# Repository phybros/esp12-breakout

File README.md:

# Breakout Board for ESP-12E and ESP-12F

This repo contains all the design files to make a breakout board for the ESP-12E and the ESP-12F which will allow you to use the ESP module on a breadboard.

The project was created using KiCAD v6.

## Design Goals

1. Breadboard compatible (i.e. 2.54mm pitch)
1. Breadboard connection doesn't cover all the breadboard holes
1. Max 2-sided PCB
1. As small (read: cheap to fabricate) as possible

## Screenshots/Photos

## License

This repo is licensed under the [Attribution-ShareAlike 4.0 license (CC BY-SA 4.0)](https://creativecommons.org/licenses/by-sa/4.0/)

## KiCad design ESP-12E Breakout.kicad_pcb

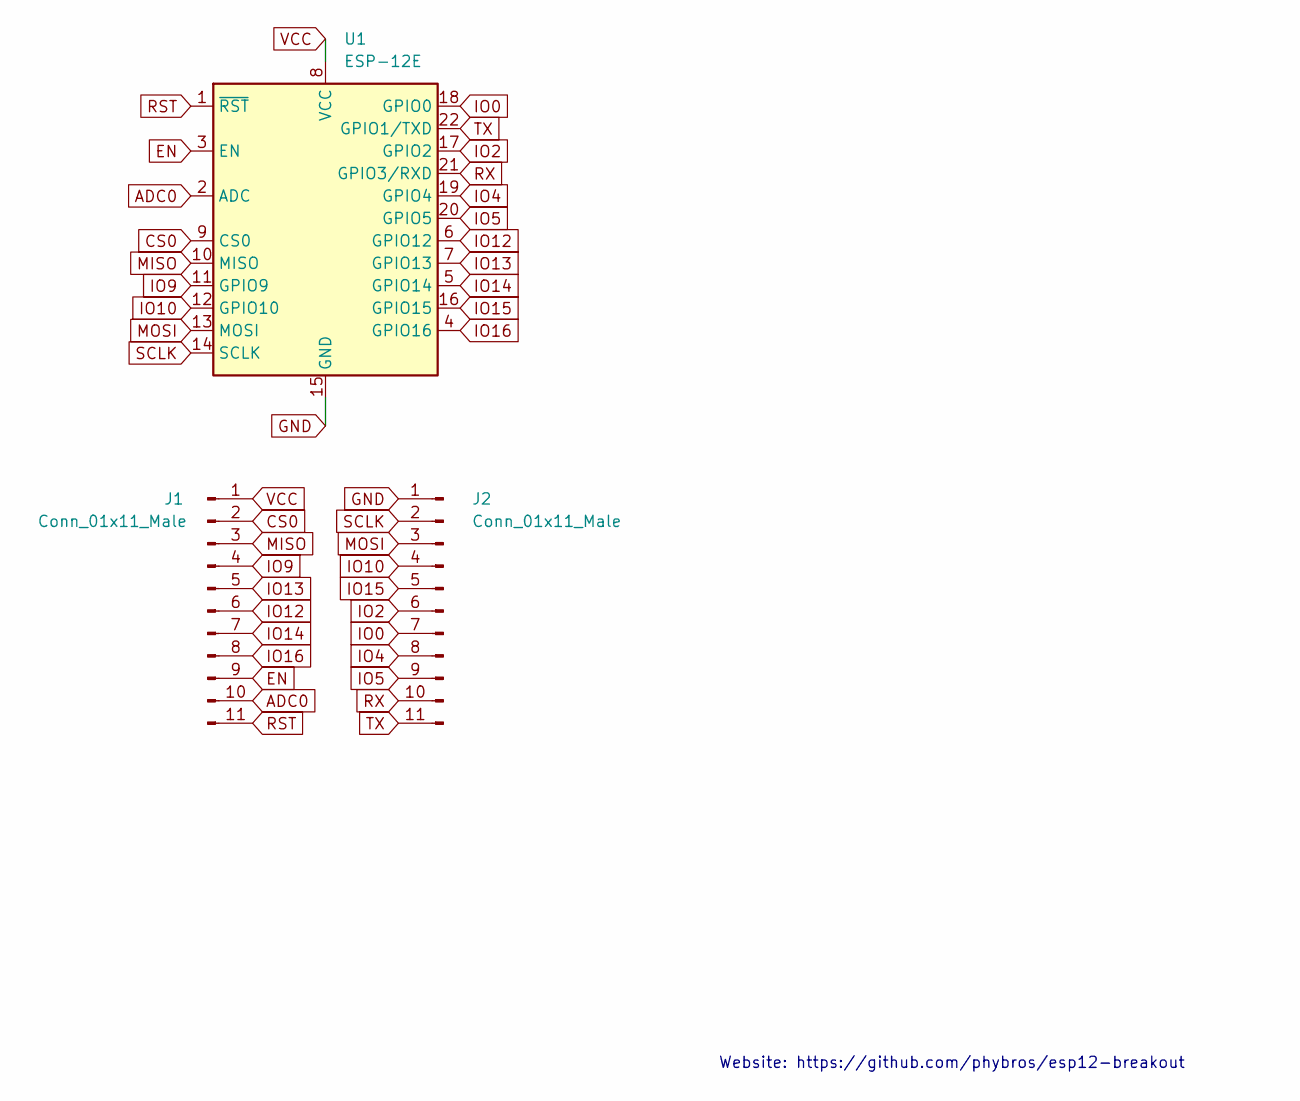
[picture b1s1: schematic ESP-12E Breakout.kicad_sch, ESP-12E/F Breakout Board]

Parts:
J1, J2: Conn_01x11_Male; PinHeader_1x11_P2.54mm_Vertical
U1: ESP-12E

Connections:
ADC0: J1.10, U1.2 (ADC)
CS0: J1.2, U1.9 (CS0)
EN: J1.9, U1.3 (EN)
GND: J2.1, U1.15 (GND)
IO0: J2.7, U1.18 (GPIO0)
IO2: J2.6, U1.17 (GPIO2)
IO4: J2.8, U1.19 (GPIO4)
IO5: J2.9, U1.20 (GPIO5)
IO9: J1.4, U1.11 (GPIO9)
IO10: J2.4, U1.12 (GPIO10)
IO12: J1.6, U1.6 (GPIO12)
IO13: J1.5, U1.7 (GPIO13)
IO14: J1.7, U1.5 (GPIO14)
IO15: J2.5, U1.16 (GPIO15)
IO16: J1.8, U1.4 (GPIO16)
MISO: J1.3, U1.10 (MISO)
MOSI: J2.3, U1.13 (MOSI)
RST: J1.11, U1.1 (~RST)
RX: J2.10, U1.21 (GPIO3/RXD)
SCLK: J2.2, U1.14 (SCLK)
TX: J2.11, U1.22 (GPIO1/TXD)
VCC: J1.1, U1.8 (VCC)

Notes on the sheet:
Website: https://github.com/phybros/esp12-breakout

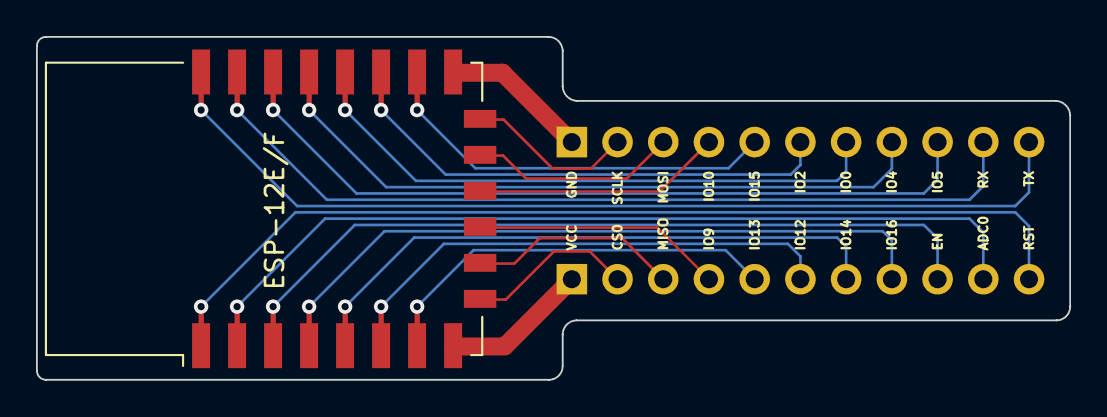
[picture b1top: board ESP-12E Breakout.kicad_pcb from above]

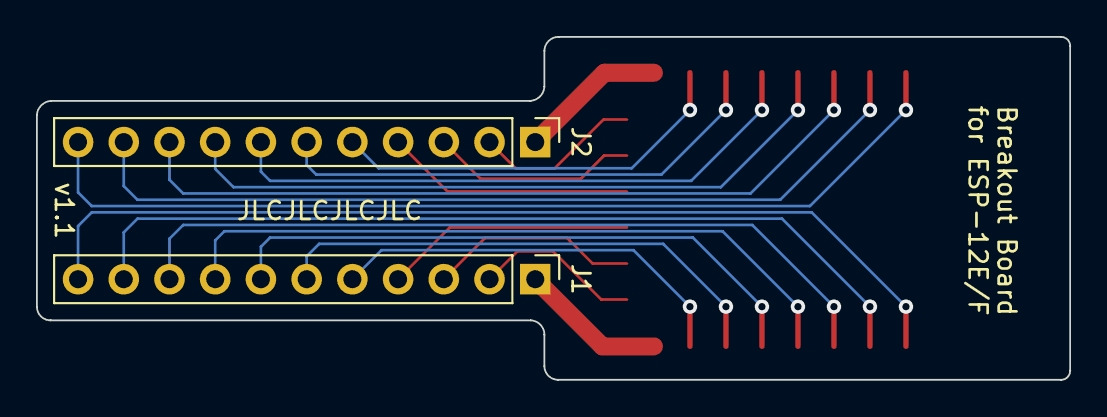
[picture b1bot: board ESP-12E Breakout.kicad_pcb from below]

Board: 2 copper layers, 57.4 x 19.0 mm, 3 parts (2 on the bottom side), 22 nets.

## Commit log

2022-10-19 Initial commit, open sourcing this design
